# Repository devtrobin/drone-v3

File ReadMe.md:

<!-- complements-r3 -->
> **Compléments du 17 octobre 2026 :** [dossier R3](Composants/complements-finalisation-r3/README.md), [assemblage FreeCAD R3](Assemblage/R3/drone-v3-r3-faisceau.FCStd). Partie fixe du faisceau définie et contrôlée ; [anomalie d’alimentation de direction](Composants/complements-finalisation-r3/alimentation-direction-a-revoir.md) et confirmations fournisseur encore ouvertes. Aucune pièce reçue, aucun essai physique réalisé.
<!-- /complements-r3 -->

<!-- finalisation-r2 -->
> **Revue du16octobre2026 :** [finalisation théoriqueR2](Composants/finalisation-theorique-r2/README.md), [visserie nominale](Composants/visserie-finale/README.md) et[assemblageR2](Assemblage/R2/README.md). Correction du dimensionnement de direction, arbres/paliers etimplantation repris. Des [conditions documentaires etde conception](Composants/finalisation-theorique-r2/conditions-restantes.md) restent ouvertes ; le véhicule complet n’est pas libéré pour fabrication/mise sous tension. Les modèles ultra détaillés précédents décriventA2-R1.
<!-- /finalisation-r2 -->

> **Surveillance M1P :** [porteuse pour fabrication de prototype et banc limit?](Composants/carte-surveillance-electrique/fabrication/README.md). Gerbers et proc?dure pr?par?s ; aucun essai r?alis?, cotes TI exactes et raccordement LiPo non lib?r?s.

# Drone terrestre V3

[Assemblage 3D complet et sous-ensembles](Assemblage/README.md) : vue FreeCAD détaillée à affichage rapide, CAO intégrale de 5 441 solides, GLB complet et cinq STEP d'implantation légers pour CAD Viewer.

Robot à châssis fabriqué, avec deux moteurs arrière et deux roues avant directrices. Raspberry Pi 5 de 4 Go pour la commande, le Wi-Fi et la vidéo. Objectifs : 40 km/h, 10–20 min à 40 km/h, au moins 45 min à 20 km/h, retour vidéo 1080p60 vers le Mac. Budget initial de 200 EUR pour le matériel neuf ; dimensionner les performances puis rechercher les économies. Aucun achat ou essai matériel.

[Composants](Composants/README.md) · [Spécifications](SPECIFICATIONS.md) · [Faisabilité](faisabilite.md) · [Index précédent archivé](archives/README-avant-correction-alimentation-2026-10-15.md).

**Alimentation révisée le 15 octobre 2026 :** Spektrum G1 SPMX50002S30H5, 2S 5 Ah IC5 ; cordon SPMXCA510 10 AWG ; principal proposé JLLN50 classe T ; départs moteurs KLKD20 ; départ Pi KLKD10 et régulateur Pololu D42V55F5 ; fil principal LAPP 6 mm² ; faisceau GPIO de signaux séparé de l’alimentation. [Audit, calculs et confirmations restantes](Composants/verification-alimentation/README.md), [raccordements](Composants/verification-alimentation/integration.md).

**Charge complétée :** Sky RC S65 conservé, cordon Beez 2B BEEC1067 XT60–EC5 et rallonge XH 2S dédiée. LiPo Balance 2S / 5 A, 42 W maximum. [Dossier de charge](Composants/cordon-charge-s65-ic5/README.md).

Caméra InnoMaker U20CAM-4M, deux Hobbywing 2435SL G3 4500 KV / WP16BL30 G2, quatre HobbyPark 63 × 26 mm, direction, réduction et autres composants documentés dans leurs dossiers. Les anciens PDF et assemblages électriques sont des références datées ; suivre la sélection révisée.

La qualification complète des protections reste ouverte : confirmations fabricant sur les supports et les brins fins, conditions de coupure DC, puis essais instrumentés. Le budget commun de 36 A est une enveloppe de dimensionnement ; 44–46 A est un scénario de pointe, pas une consommation mesurée de roulage. Les autonomies demandées nécessitent une puissance moyenne totale nettement plus basse.

**Ordre retenu :** [carte de surveillance, support caméra, supports capteurs, châssis, puis visserie finale](PLAN-CONCEPTION.md). La [surveillance M1 à modules existants](Composants/carte-surveillance-electrique/README.md) dispose de son schéma, routage, notice et STEP de porteuse avec gabarits. Contrôles KiCad réussis ; disponibilité, cotes EVM et qualification matérielle restent ouvertes.

[Mesure de vitesse des deux roues arrière](Composants/capteurs-vitesse/README.md) : deux capteurs Hall, deux aimants par roue, rappels et découplages ; extension GPIO à13 contacts. Implantation finale avec le châssis.

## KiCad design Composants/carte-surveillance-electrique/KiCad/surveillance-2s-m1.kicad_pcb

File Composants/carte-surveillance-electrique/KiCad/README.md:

# KiCad - Surveillance 2S M1

Ouvrir [surveillance-2s-m1.kicad_pro](surveillance-2s-m1.kicad_pro). [Schéma](surveillance-2s-m1.kicad_sch), [PCB routé](surveillance-2s-m1.kicad_pcb), [schéma vectoriel](vues/surveillance-2s-m1.svg), [routage](vues/routage.svg), [montage](vues/montage.svg), [dessus](vues/cuivre-dessus.svg), [dessous](vues/cuivre-dessous.svg), [CSV porteuse](nomenclature.csv), [CSV assemblage complet](../nomenclature-assemblage.csv).

41 composants/connexions sur porteuse, dont R7/R8 DNP ; 26 nets ; PCB 140 x 75 x 1,6, deux couches. Pistes 0,20, isolement minimal 0,15, cuivre supposé 35 micromètres, vias 0,60/0,30. Ces règles ne sont pas une procédure d'usinage CNC. Les empreintes locales Nano454 et TMR1 et les symboles de blocs sont inclus ; les autres empreintes sont celles des bibliothèques standard KiCad 10. Les symboles de blocs représentent les fonctions et pins des interfaces, pas les composants internes des modules commerciaux.

**Contrôle KiCad 10.0.7 : ERC 0, DRC 0, aucun élément non connecté, aucune divergence de parité schéma/PCB.** Netlist XML comparée indépendamment aux connexions attendues. Rapports complets dans [verification](../verification/controle-kicad.json), sans exclusions ajoutées pour masquer les défauts. Les recommandations du fabricant et le montage réel restent à qualifier.

J3/J4 et J5 sont des départs de faisceaux vers les modules, pas des empreintes où enficher directement un EVM ou un Pololu. Les résistances de seuil restent sur les deux EVM, hors porteuse. RA0/RA1/RA2 au pack et FAUX près de sa dérivation ne sont pas placés sur ce PCB. R7/R8 sont achetées mais montées côté Pi ; leurs pads porteuse restent vides.

Génération reproductible depuis la racine V3 : `D:/KiCAD/bin/python.exe tools/build_monitor_kicad.py`. Contrôles : `tools/temp/cad-env/Scripts/python.exe tools/check_monitor_kicad.py`. Les paramètres et la connectivité sont dans le script et les JSON. Les vues de cuivre sont des documents de revue ; il faut une revue d'empreintes et les essais décrits avant de libérer une fabrication. Aucun Gerber n'est présenté comme validé pour production.

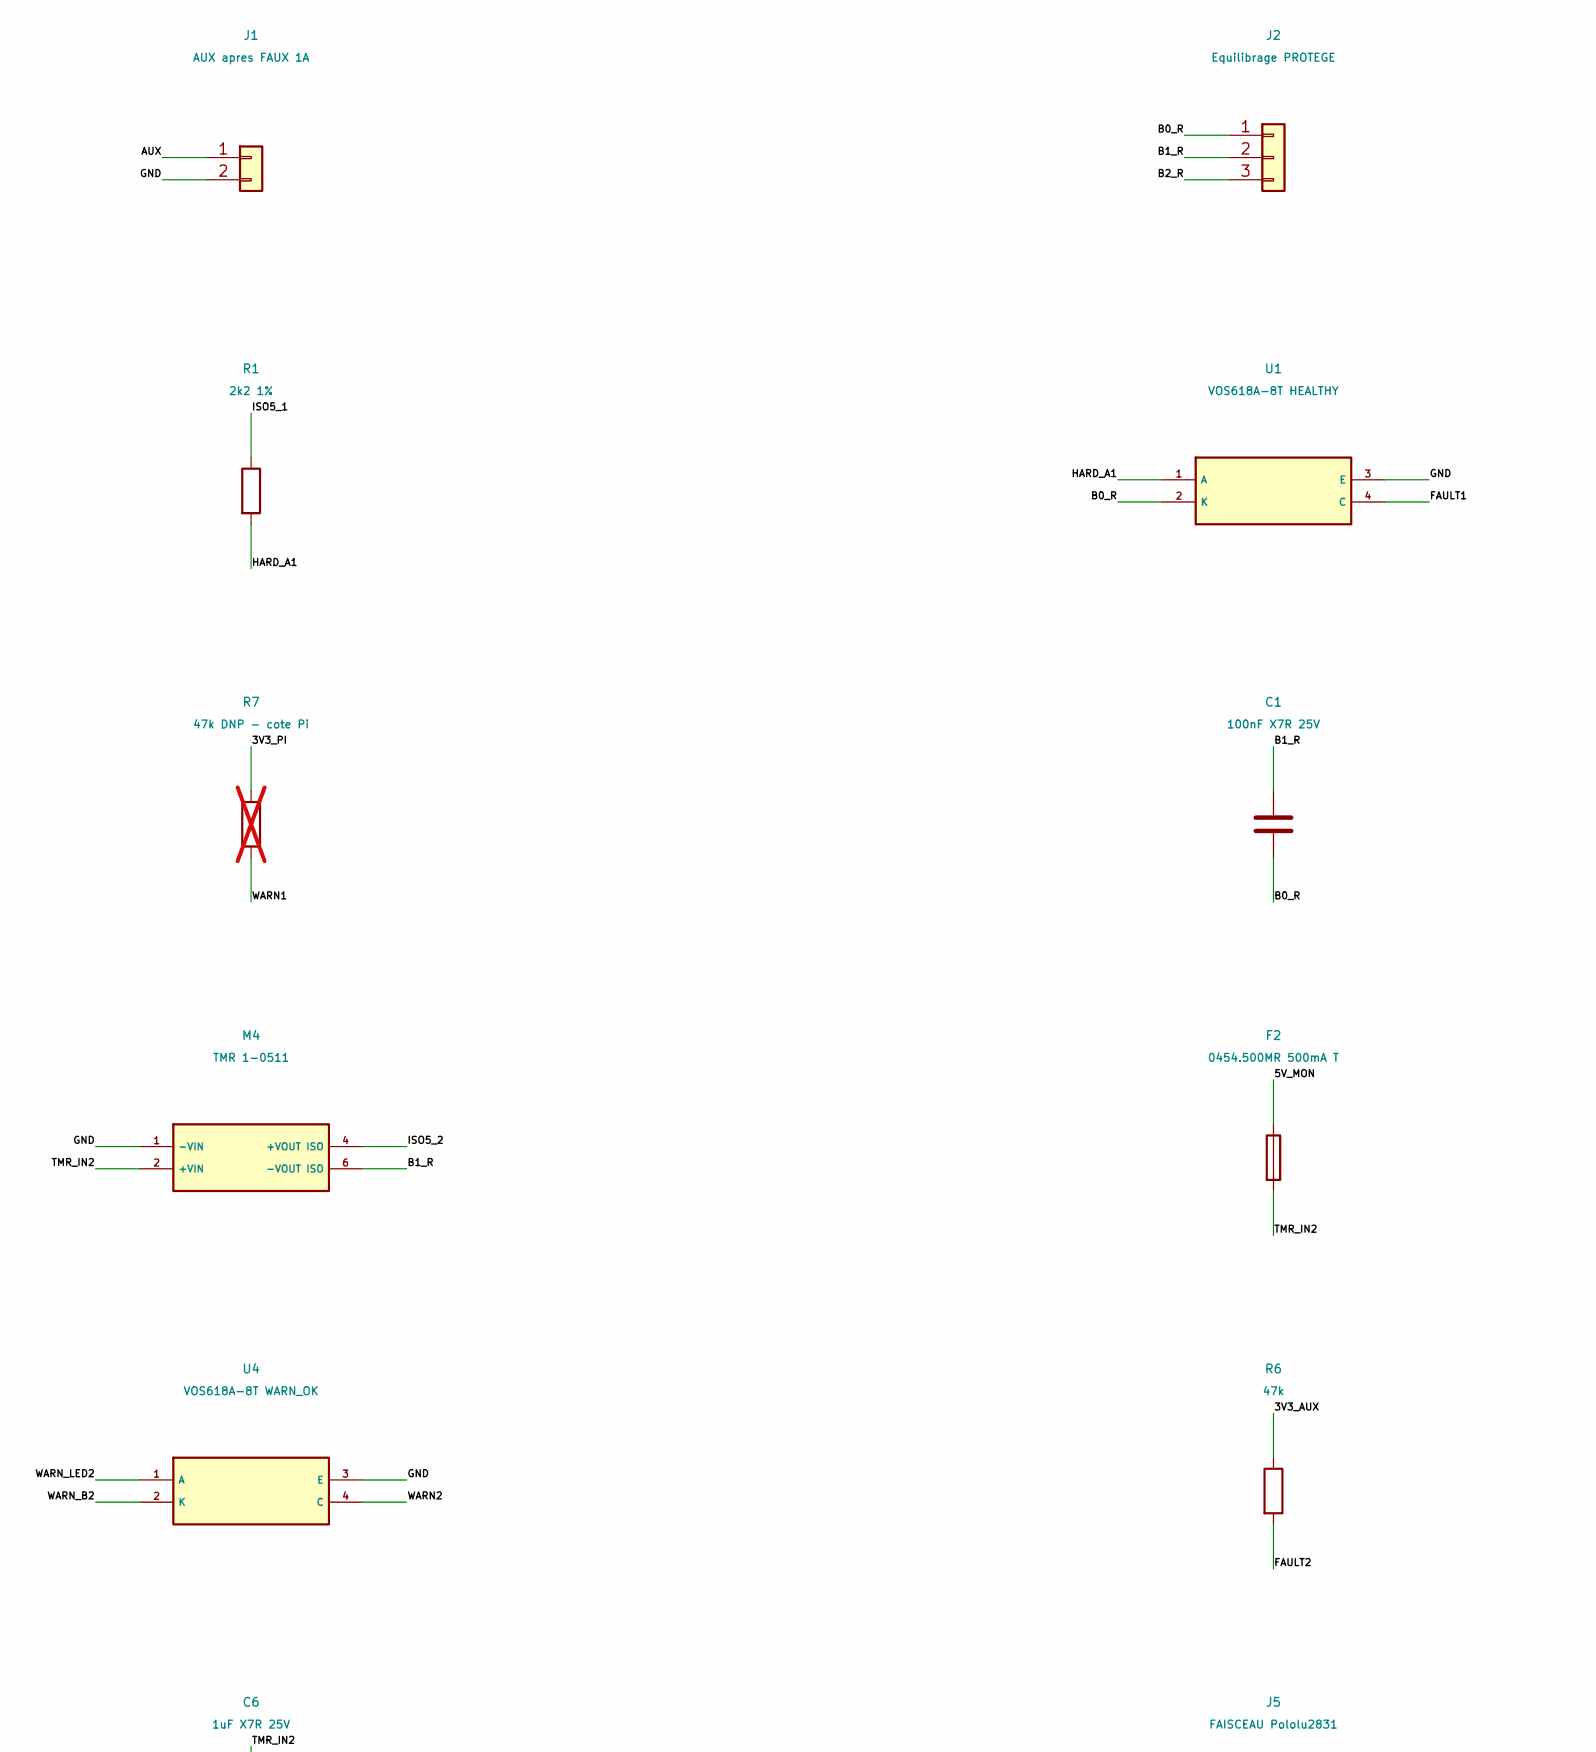
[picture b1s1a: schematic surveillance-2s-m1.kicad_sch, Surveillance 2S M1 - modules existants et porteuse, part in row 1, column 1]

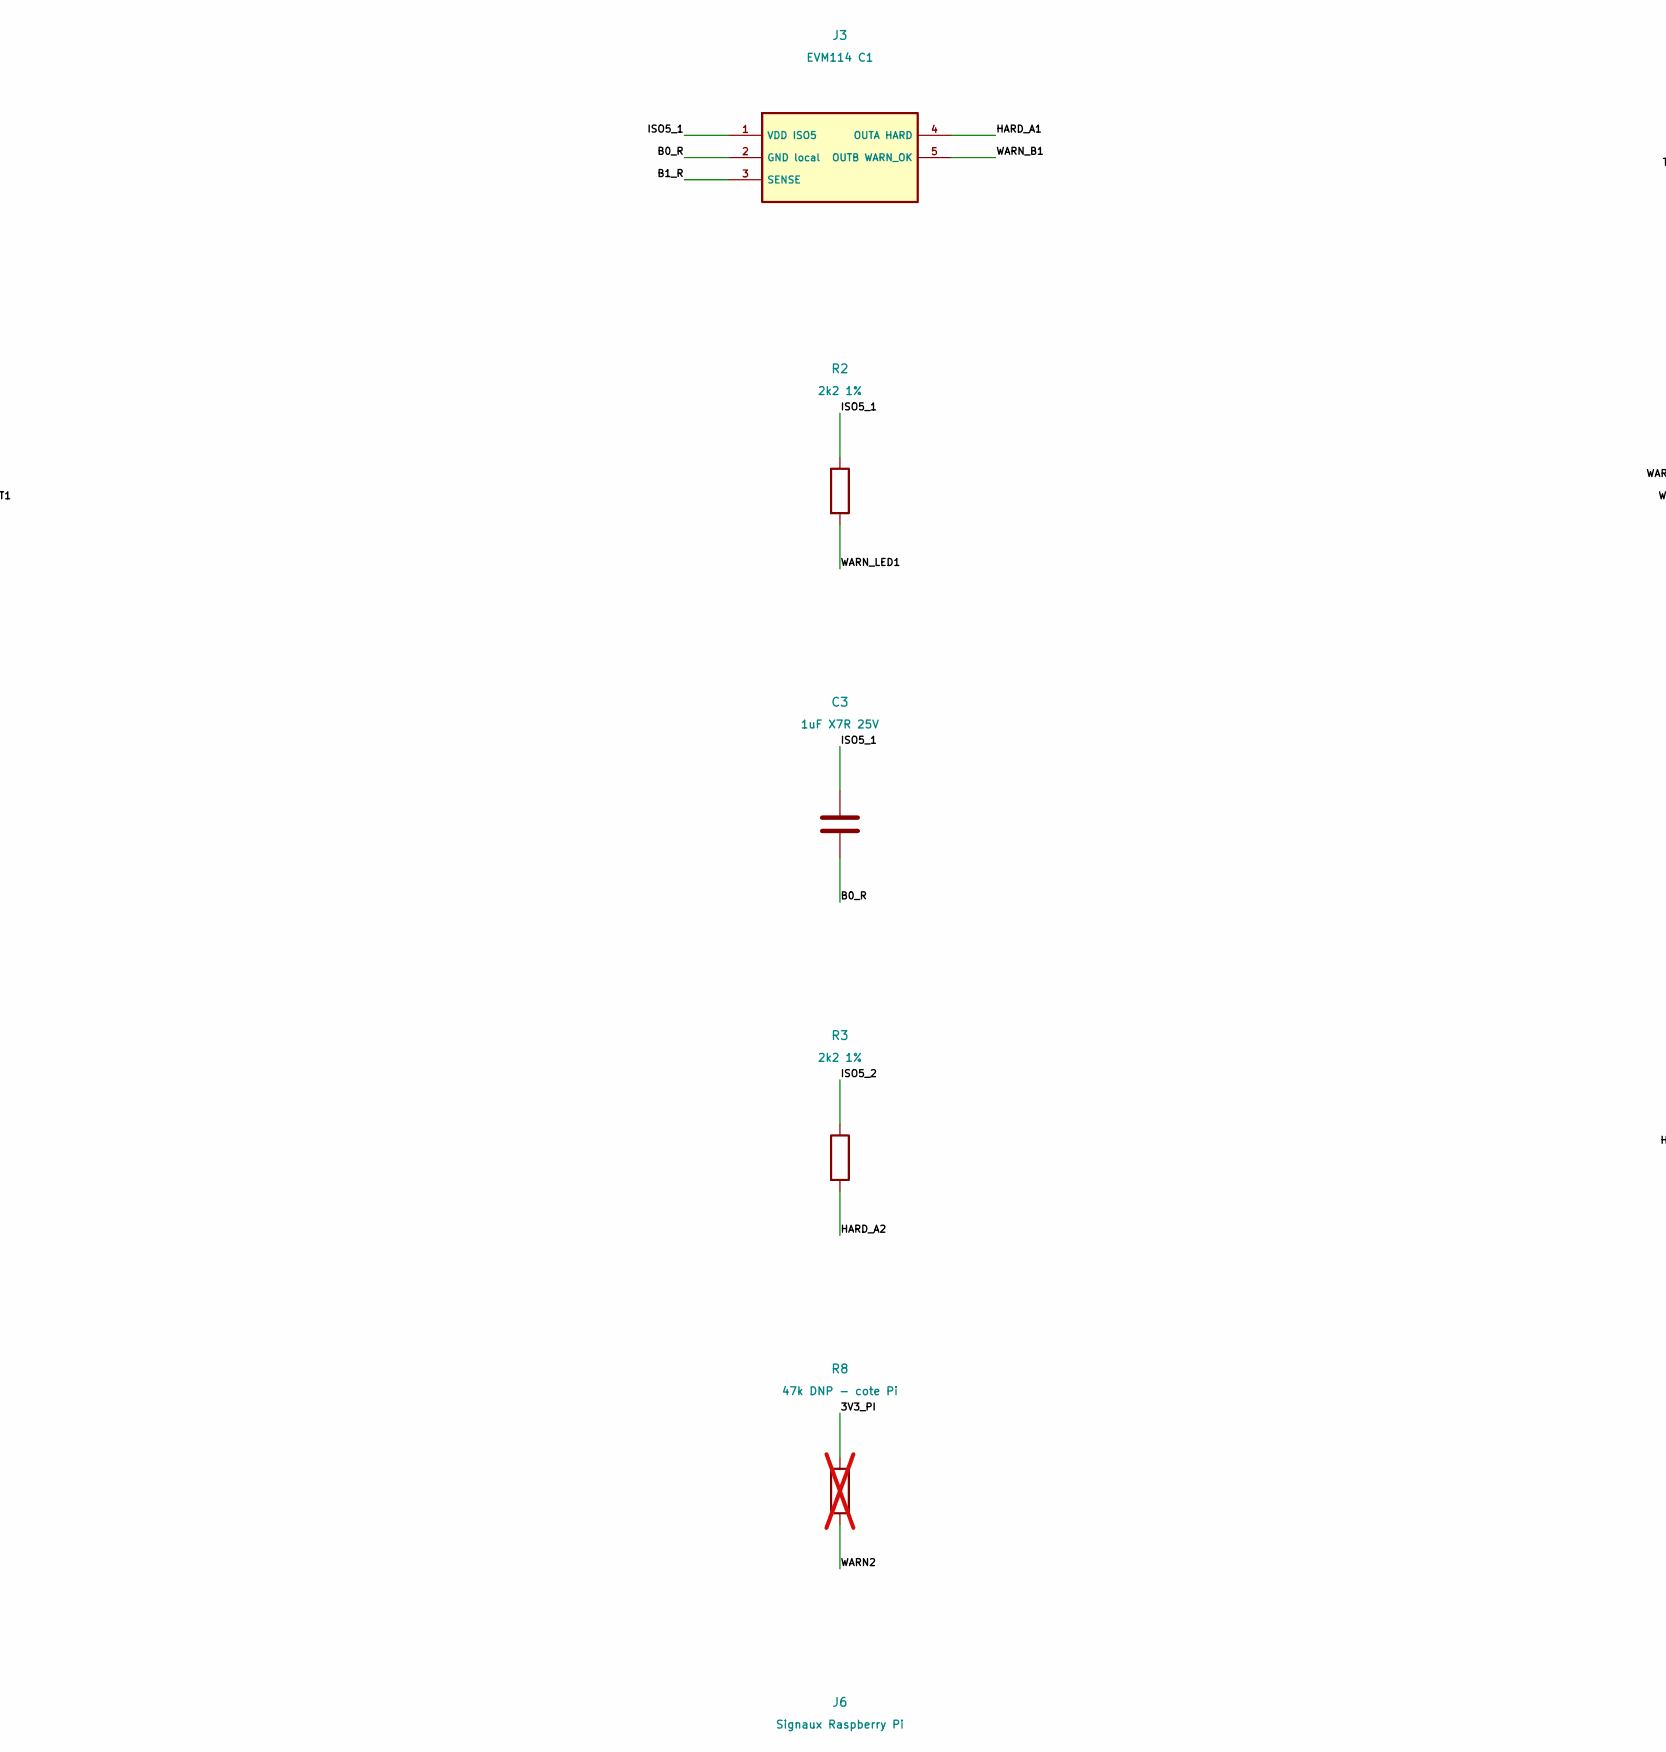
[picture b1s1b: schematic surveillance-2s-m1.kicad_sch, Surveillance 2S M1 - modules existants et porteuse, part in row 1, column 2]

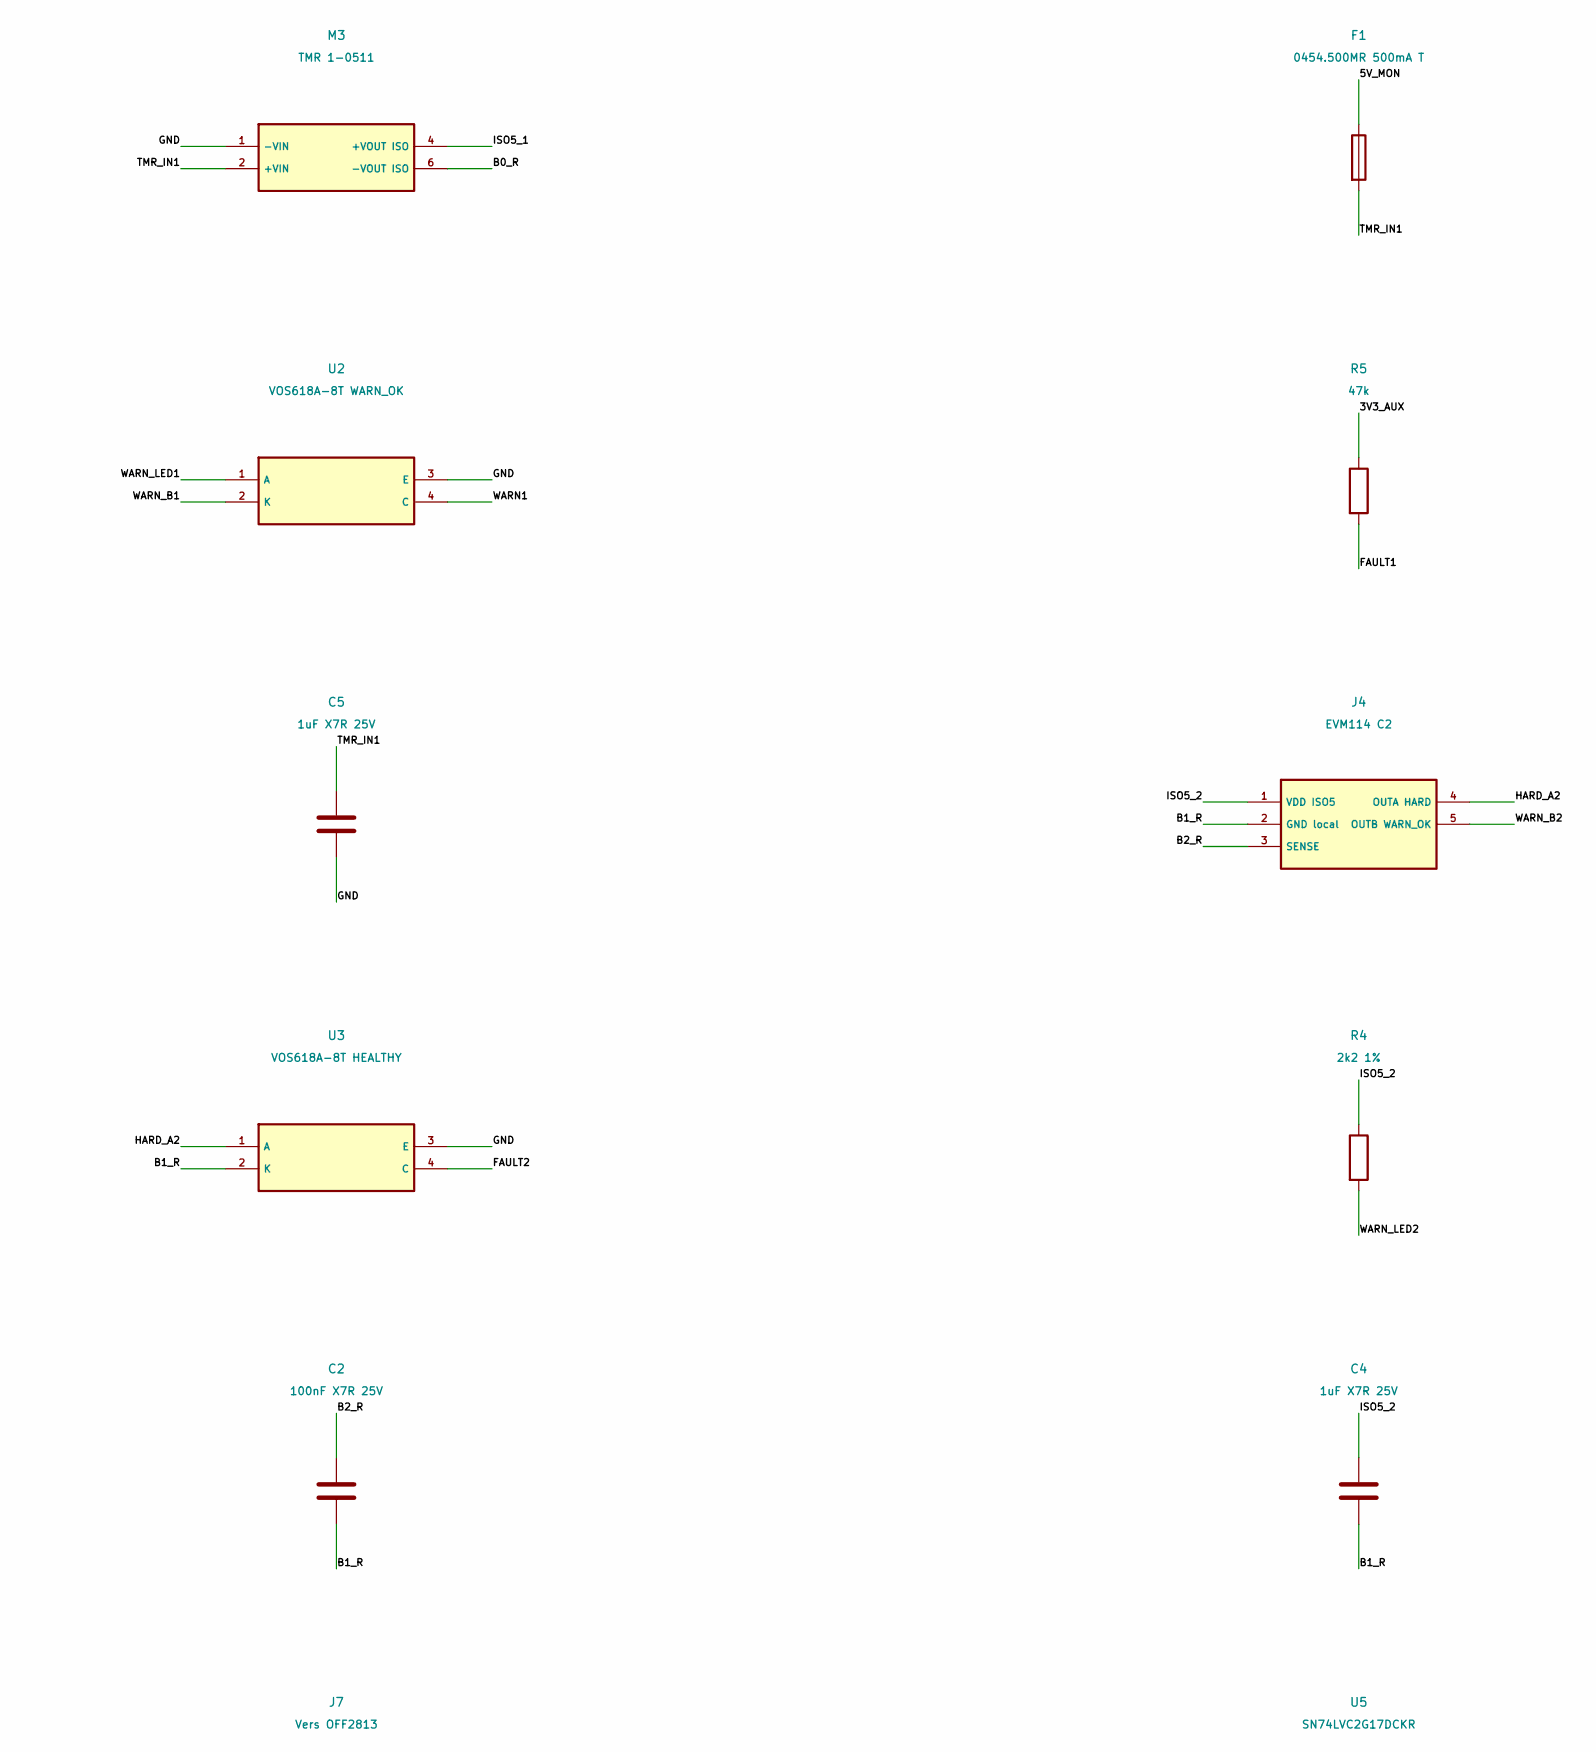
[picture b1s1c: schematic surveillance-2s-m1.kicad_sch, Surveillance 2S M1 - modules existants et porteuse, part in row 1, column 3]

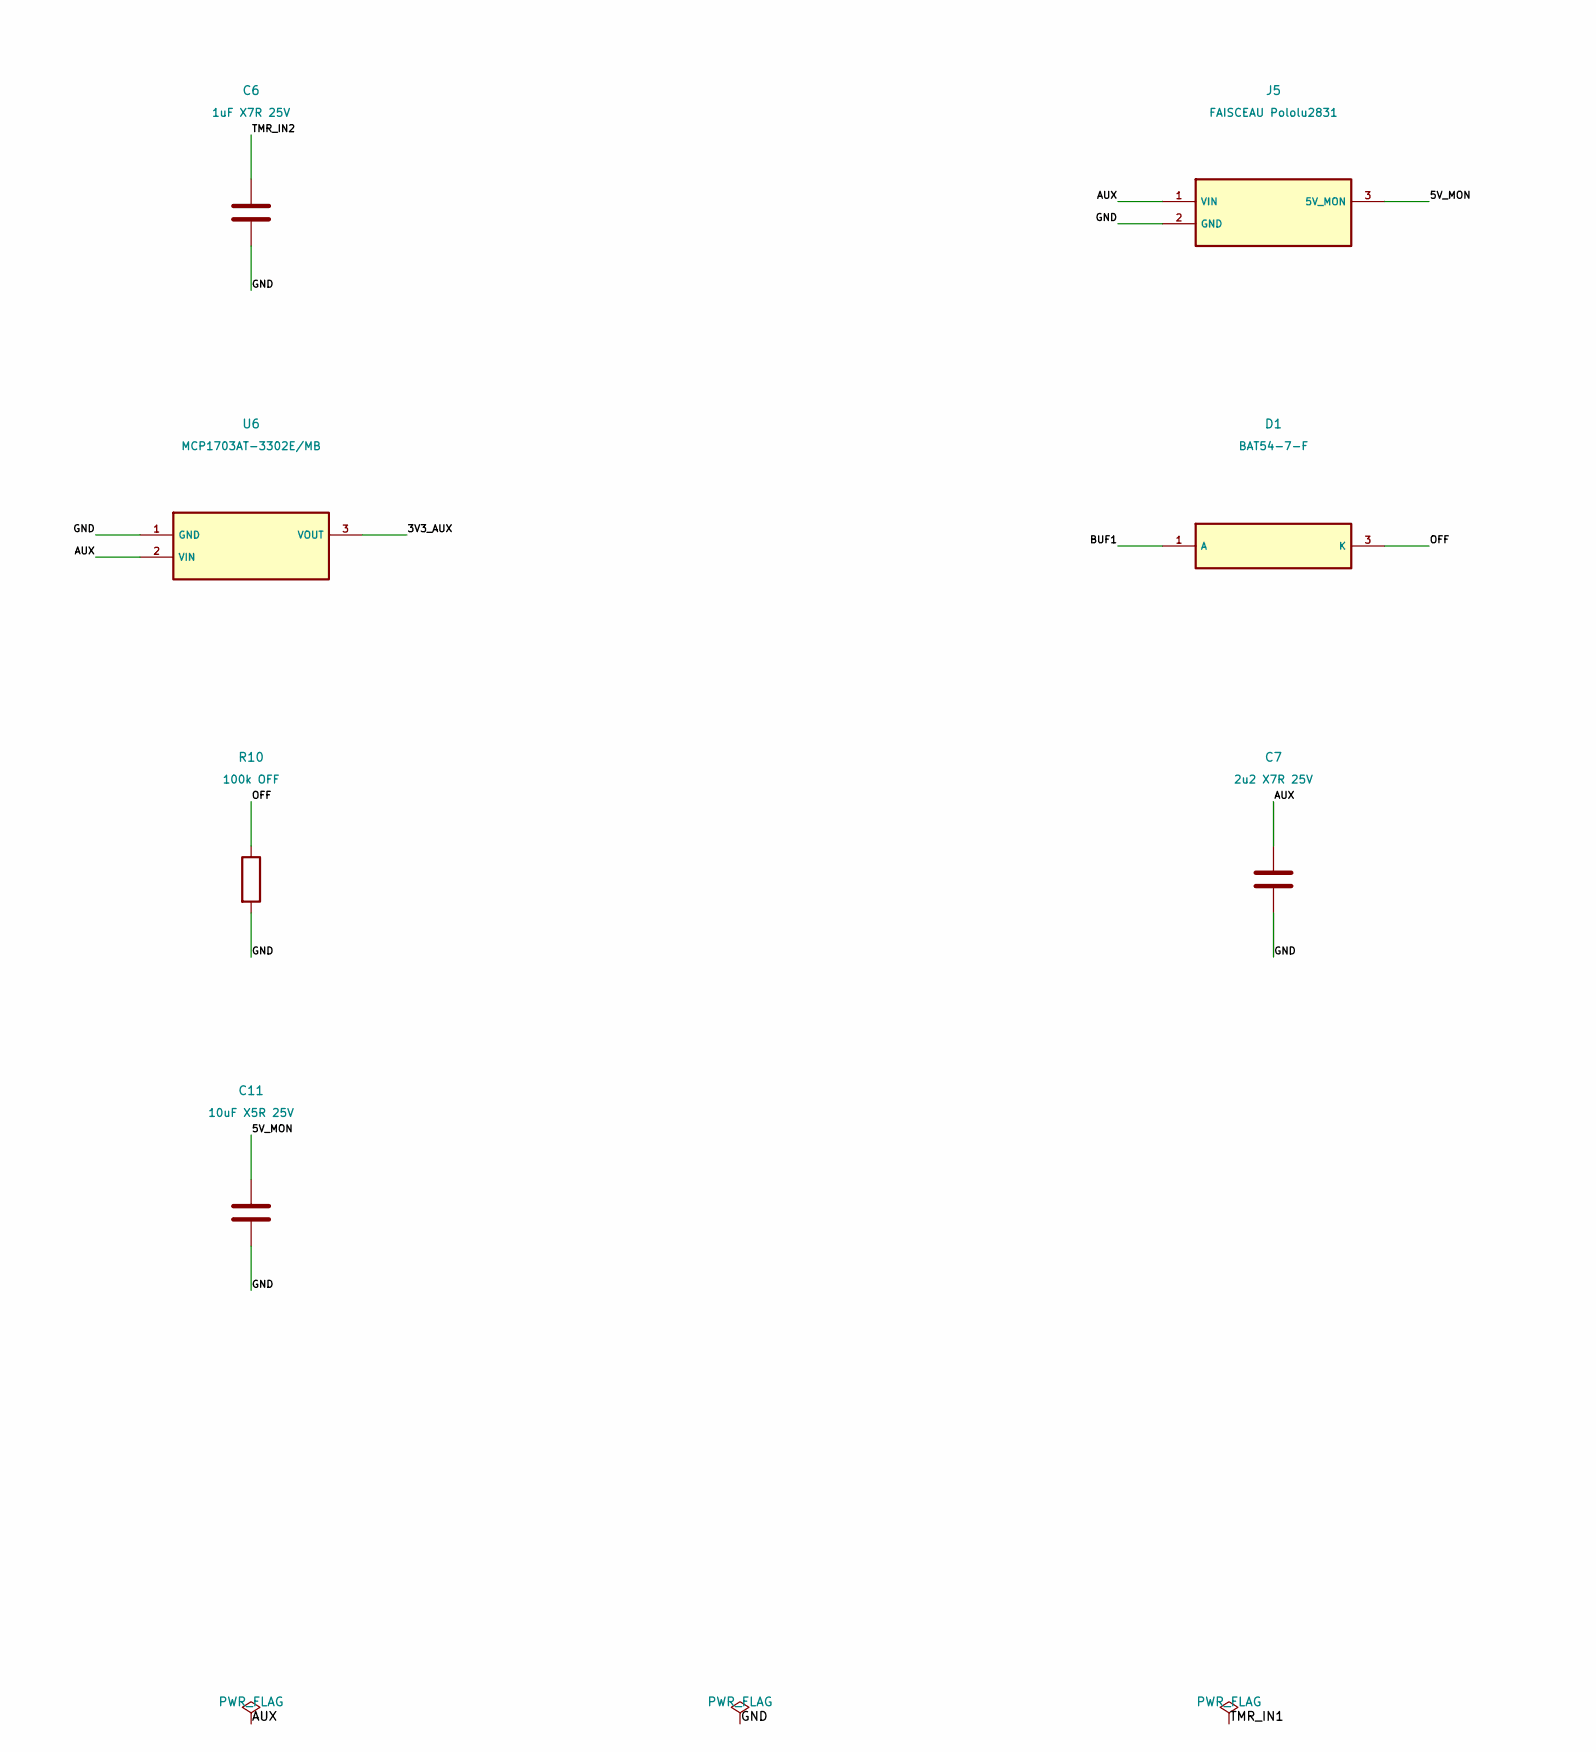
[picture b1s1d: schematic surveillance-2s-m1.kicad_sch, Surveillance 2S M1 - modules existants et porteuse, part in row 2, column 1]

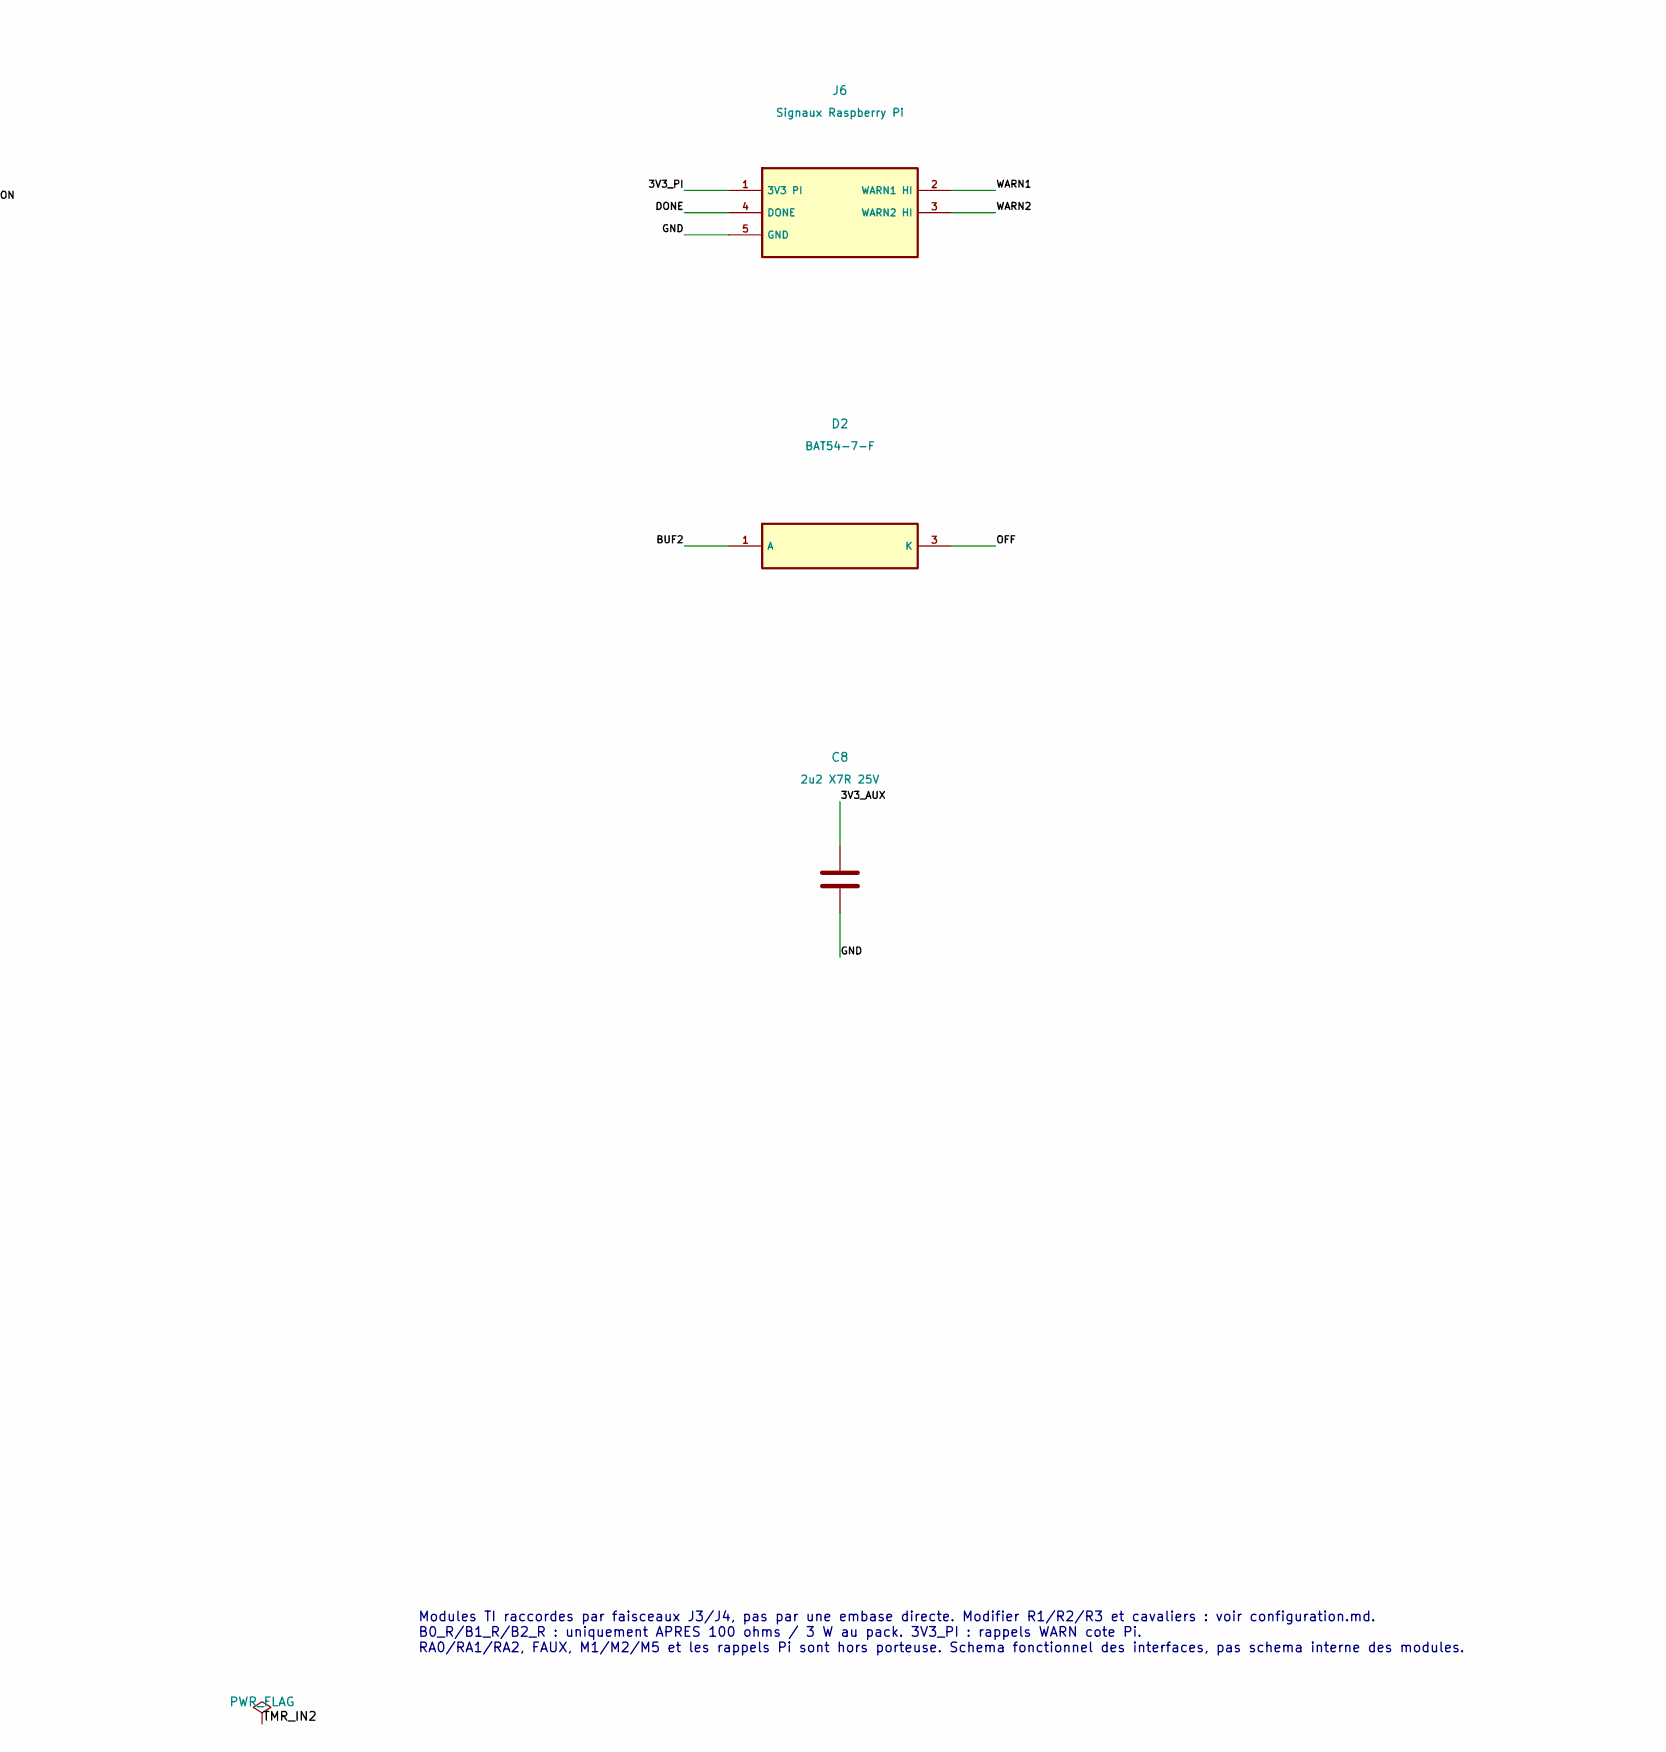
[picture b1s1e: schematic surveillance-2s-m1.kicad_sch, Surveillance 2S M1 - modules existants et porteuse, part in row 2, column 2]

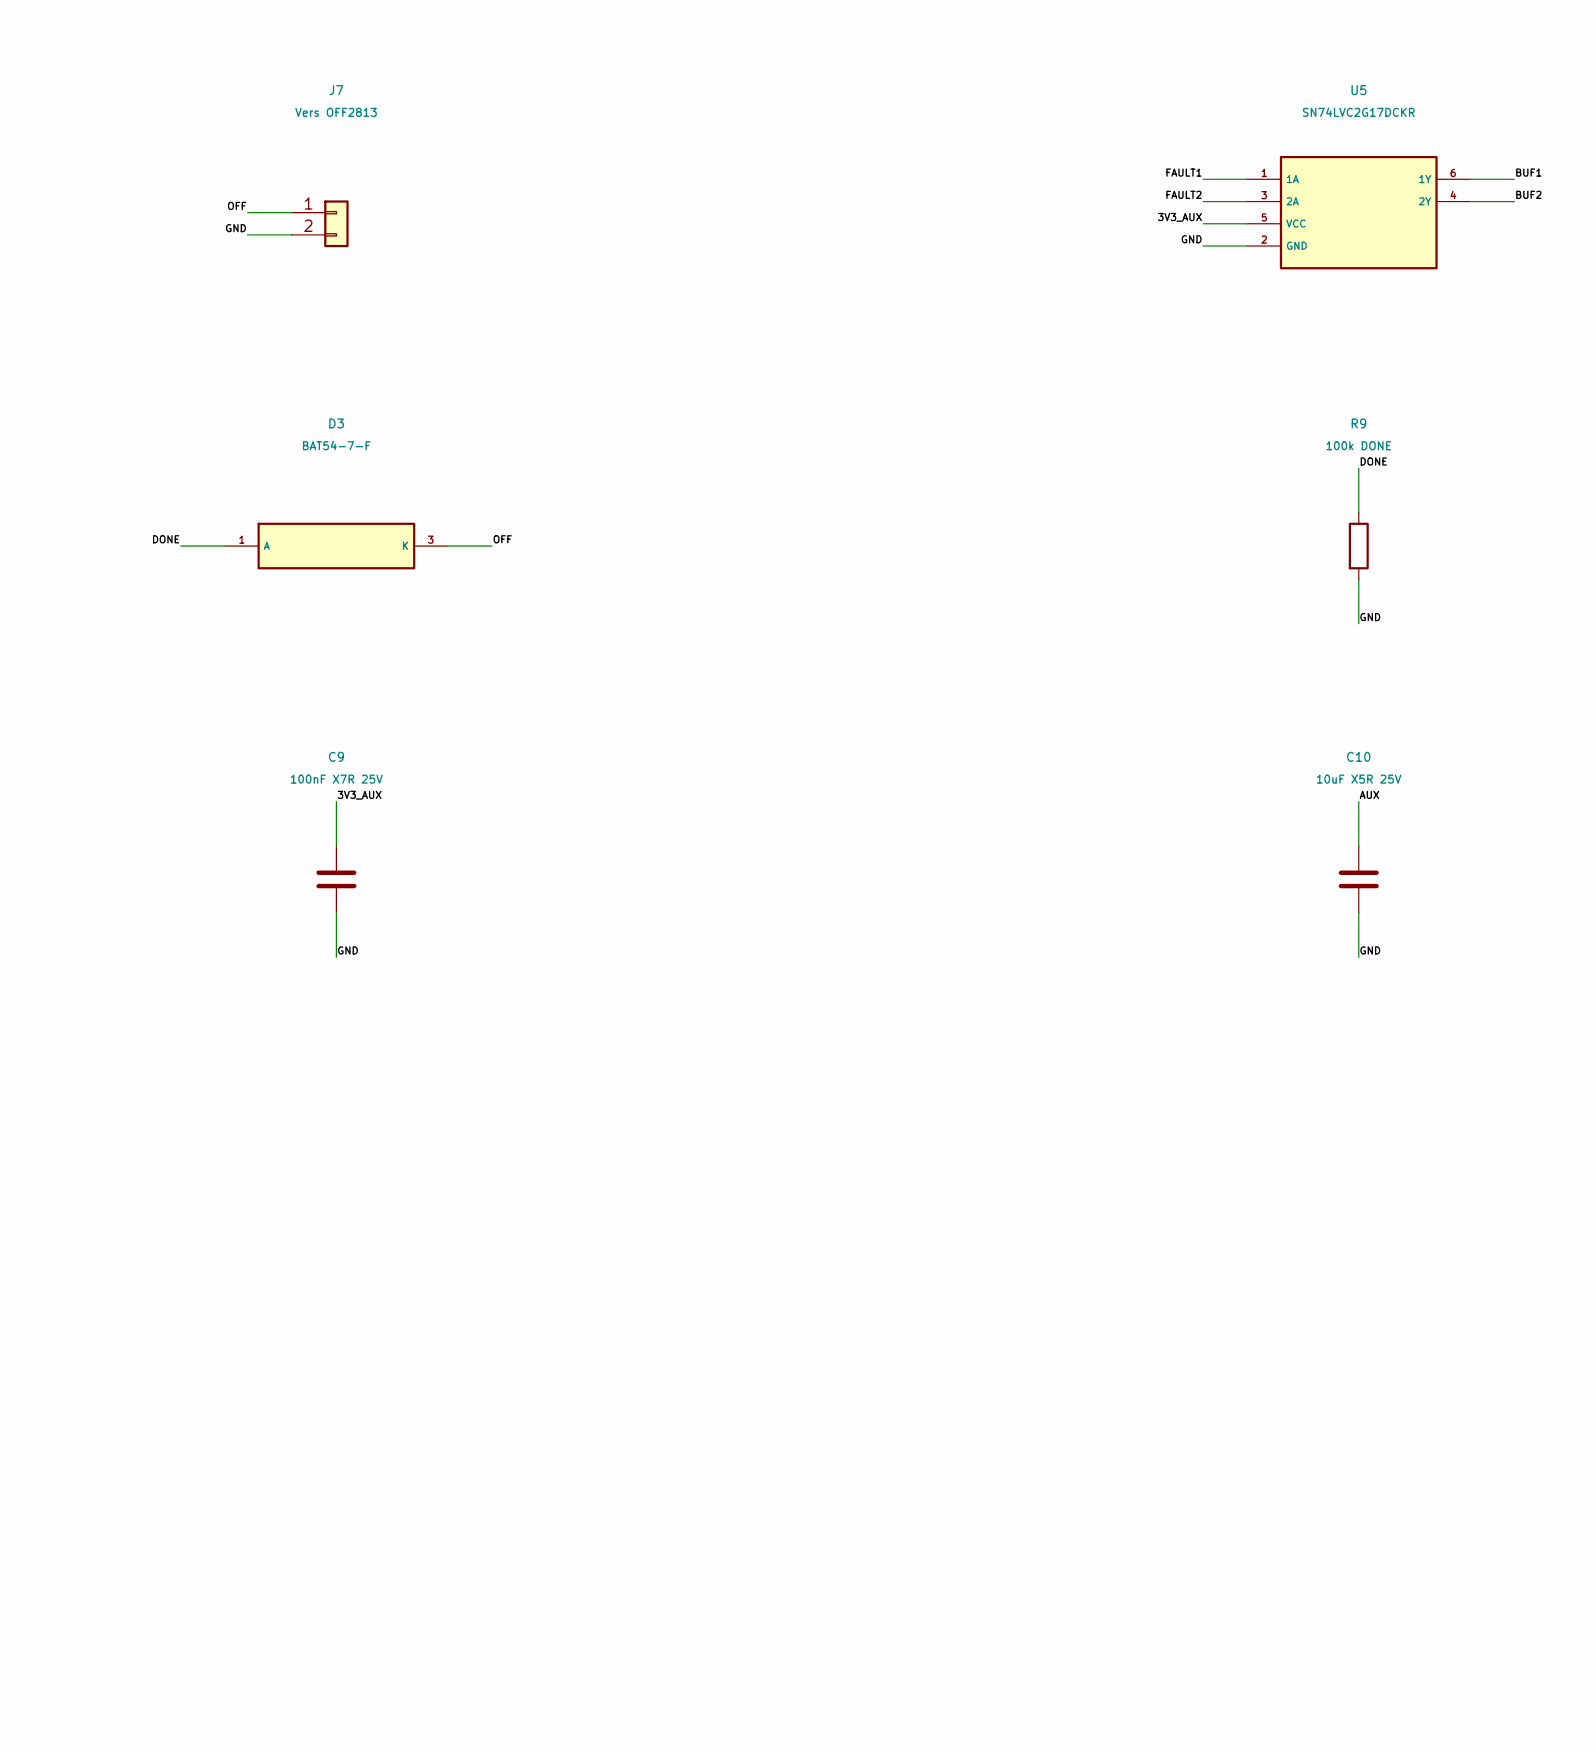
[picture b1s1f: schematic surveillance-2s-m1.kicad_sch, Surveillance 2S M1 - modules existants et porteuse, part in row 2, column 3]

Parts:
C1, C2, C9: 100nF X7R 25V; C_0805_2012Metric
C3, C4, C5, C6: 1uF X7R 25V; C_0805_2012Metric
C7, C8: 2u2 X7R 25V; C_0805_2012Metric
C10, C11: 10uF X5R 25V; C_0805_2012Metric
D1, D2, D3: BAT54-7-F; SOT-23
F1, F2: 0454.500MR 500mA T; Nano454
J1: AUX apres FAUX 1A; JST_XH_B2B-XH-A_1x02_P2.50mm_Vertical
J2: Equilibrage PROTEGE; JST_XH_B3B-XH-A_1x03_P2.50mm_Vertical
J3: EVM114 C1; JST_XH_B5B-XH-A_1x05_P2.50mm_Vertical
J4: EVM114 C2; JST_XH_B5B-XH-A_1x05_P2.50mm_Vertical
J5: FAISCEAU Pololu2831; JST_XH_B3B-XH-A_1x03_P2.50mm_Vertical
J6: Signaux Raspberry Pi; JST_XH_B5B-XH-A_1x05_P2.50mm_Vertical
J7: Vers OFF2813; JST_XH_B2B-XH-A_1x02_P2.50mm_Vertical
M3, M4: TMR 1-0511; TMR1
R1, R2, R3, R4: 2k2 1%; R_0805_2012Metric
R5, R6: 47k; R_0805_2012Metric
R7, R8: 47k DNP - cote Pi; R_0805_2012Metric; not fitted
R9: 100k DONE; R_0805_2012Metric
R10: 100k OFF; R_0805_2012Metric
U1, U3: VOS618A-8T HEALTHY; SSOP-4_4.4x2.6mm_P1.27mm
U2, U4: VOS618A-8T WARN_OK; SSOP-4_4.4x2.6mm_P1.27mm
U5: SN74LVC2G17DCKR; SOT-363_SC-70-6
U6: MCP1703AT-3302E/MB; SOT-89-3

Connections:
/3V3_AUX: C8.1, C9.1, R5.1, R6.1, U5.5 (VCC), U6.3 (VOUT)
/3V3_PI: J6.1 (3V3 PI), R7.1, R8.1
/5V_MON: C11.1, F1.1, F2.1, J5.3 (5V_MON)
/AUX: C7.1, C10.1, J1.1, J5.1 (VIN), U6.2 (VIN)
/B0_R: C1.2, C3.2, J2.1, J3.2 (GND local), M3.6 (-VOUT ISO), U1.2 (K)
/B1_R: C1.1, C2.2, C4.2, J2.2, J3.3 (SENSE), J4.2 (GND local), M4.6 (-VOUT ISO), U3.2 (K)
/B2_R: C2.1, J2.3, J4.3 (SENSE)
/BUF1: D1.1 (A), U5.6 (1Y)
/BUF2: D2.1 (A), U5.4 (2Y)
/DONE: D3.1 (A), J6.4 (DONE), R9.1
/FAULT1: R5.2, U1.4 (C), U5.1 (1A)
/FAULT2: R6.2, U3.4 (C), U5.3 (2A)
/GND: C5.2, C6.2, C7.2, C8.2, C9.2, C10.2, C11.2, J1.2, J5.2 (GND), J6.5 (GND), J7.2, M3.1 (-VIN), M4.1 (-VIN), R9.2, R10.2, U1.3 (E), U2.3 (E), U3.3 (E), U4.3 (E), U5.2 (GND), U6.1 (GND)
/HARD_A1: J3.4 (OUTA HARD), R1.2, U1.1 (A)
/HARD_A2: J4.4 (OUTA HARD), R3.2, U3.1 (A)
/ISO5_1: C3.1, J3.1 (VDD ISO5), M3.4 (+VOUT ISO), R1.1, R2.1
/ISO5_2: C4.1, J4.1 (VDD ISO5), M4.4 (+VOUT ISO), R3.1, R4.1
/OFF: D1.3 (K), D2.3 (K), D3.3 (K), J7.1, R10.1
/TMR_IN1: C5.1, F1.2, M3.2 (+VIN)
/TMR_IN2: C6.1, F2.2, M4.2 (+VIN)
/WARN1: J6.2 (WARN1 HI), R7.2, U2.4 (C)
/WARN2: J6.3 (WARN2 HI), R8.2, U4.4 (C)
/WARN_B1: J3.5 (OUTB WARN_OK), U2.2 (K)
/WARN_B2: J4.5 (OUTB WARN_OK), U4.2 (K)
/WARN_LED1: R2.2, U2.1 (A)
/WARN_LED2: R4.2, U4.1 (A)

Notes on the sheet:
Modules TI raccordes par faisceaux J3/J4, pas par une embase directe. Modifier R1/R2/R3 et cavaliers : voir configuration.md. B0_R/B1_R/B2_R : uniquement APRES 100 ohms / 3 W au pack. 3V3_PI : rappels WARN cote Pi. RA0/RA1/RA2, FAUX, M1/M2/M5 et les rappels Pi sont hors porteuse. Schema fonctionnel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

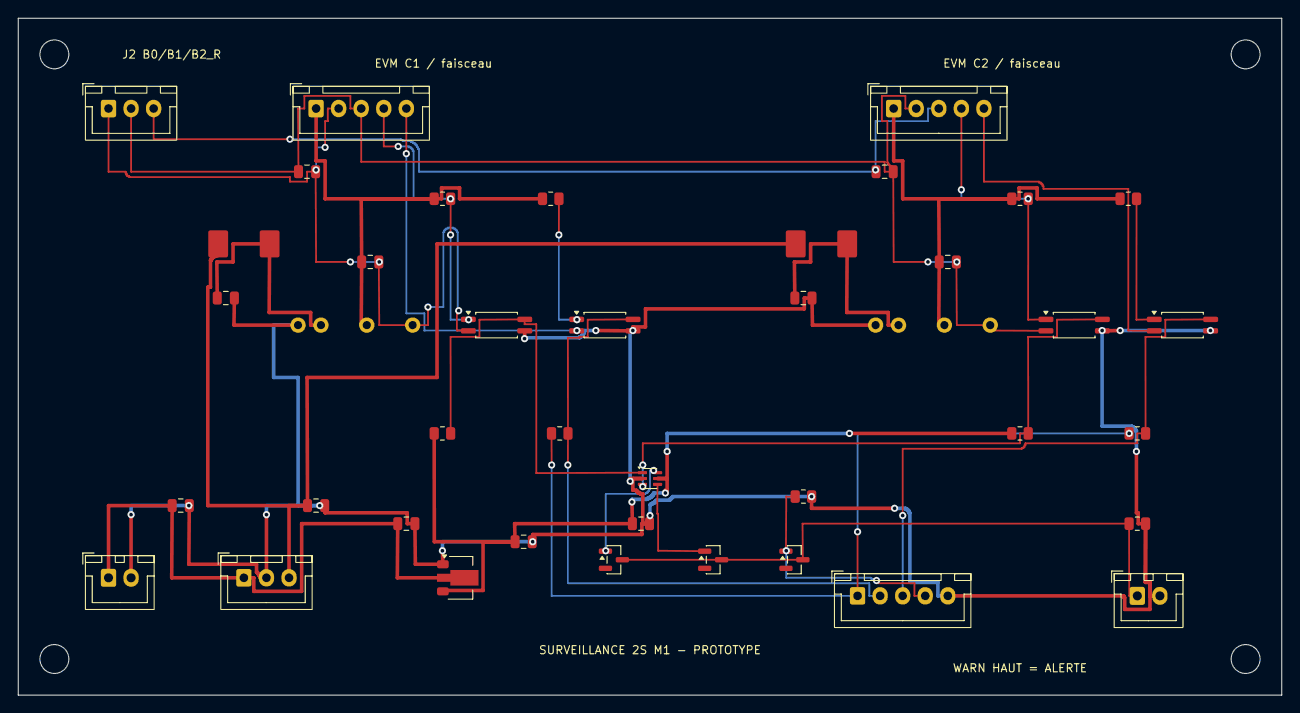
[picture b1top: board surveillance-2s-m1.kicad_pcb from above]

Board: 2 copper layers, 140.0 x 75.0 mm, 45 parts (0 on the bottom side), 26 nets.

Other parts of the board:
H1, H2, H3, H4: MountingHole_3.2mm_M3

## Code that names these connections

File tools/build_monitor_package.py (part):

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
## Interface du Pi et OFF

J6 : 1 = 3V3_PI (pin physique 1), 2 = WARN1 (GPIO17/pin11), 3 = WARN2 (GPIO27/pin13), 4 = DONE (GPIO22/pin15), 5 = GND (D-, point système existant). Le signal GND de surveillance utilise une dérivation du retour de référence existant ; ne pas prendre B0_R comme masse.

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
